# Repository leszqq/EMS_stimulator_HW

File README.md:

# EMS_stimulator_HW
Hardware for battery powered neuromuscular stimulator

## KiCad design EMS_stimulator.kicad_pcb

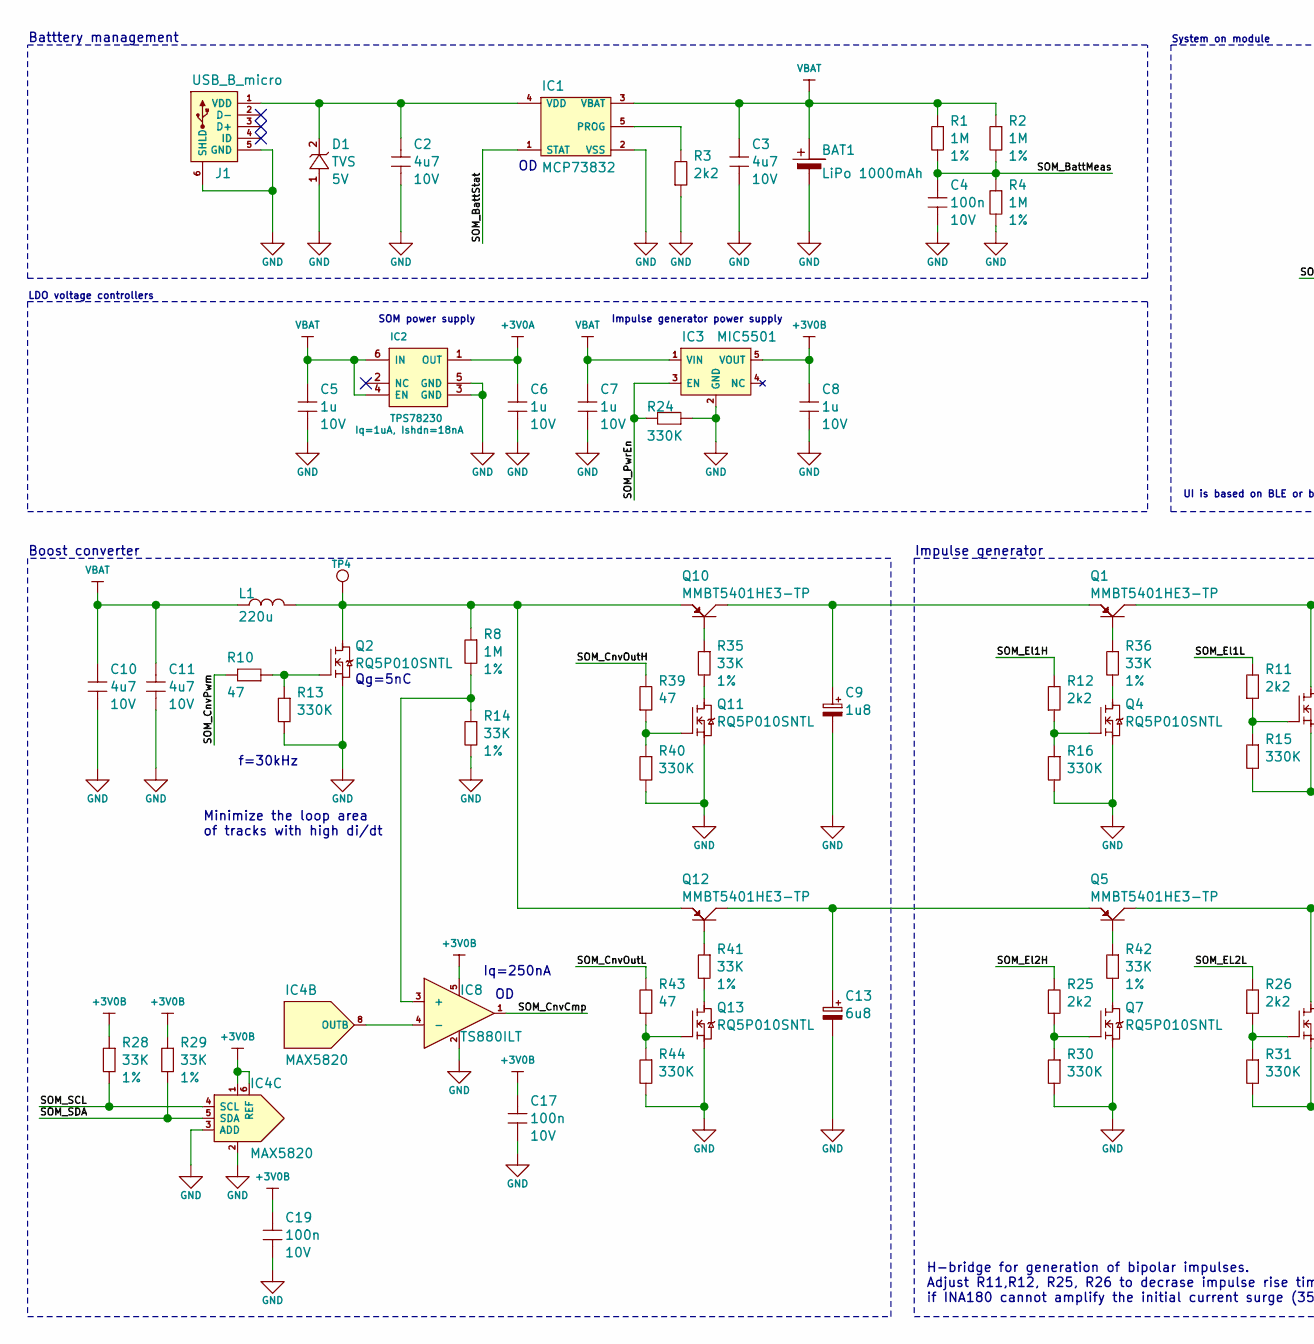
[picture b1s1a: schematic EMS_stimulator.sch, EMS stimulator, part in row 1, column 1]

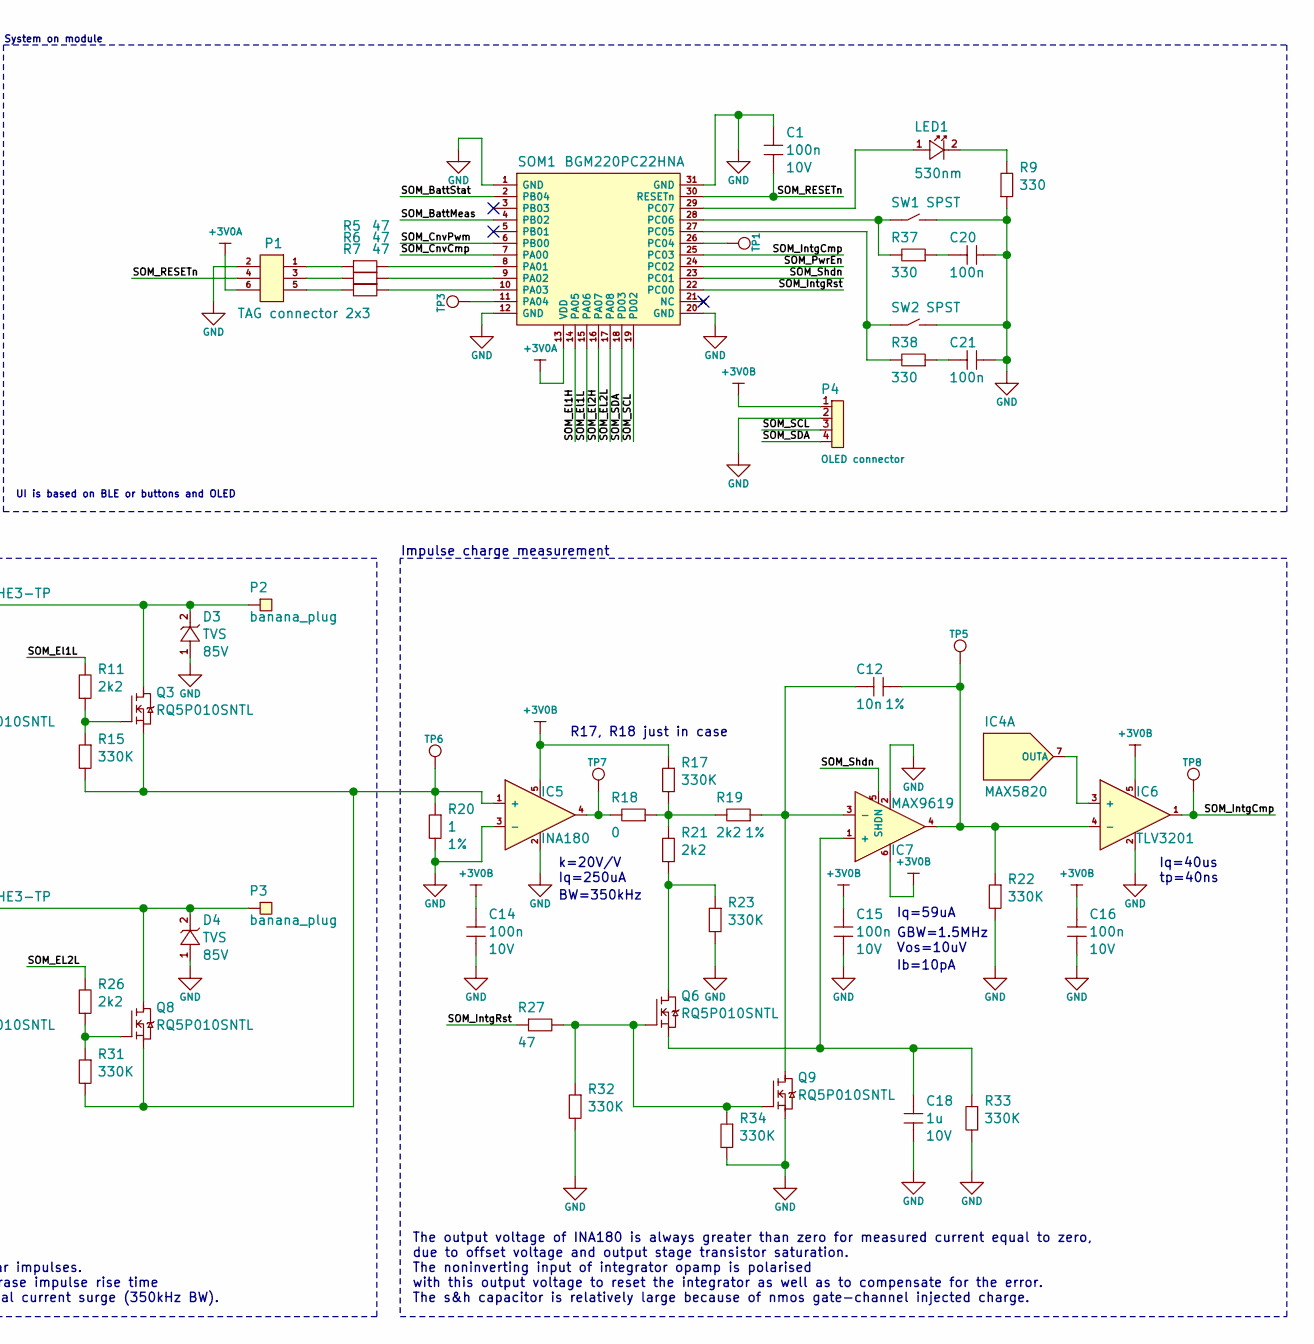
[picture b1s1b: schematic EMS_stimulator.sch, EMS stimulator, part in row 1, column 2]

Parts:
BAT1: LiPo 1000mAh; wire_solder_tht_pad-x2
C1, C4, C14, C15, C16, C17, C19, C20, C21: 100n; C0402
C2, C3, C10, C11: 4u7; C0402
C5, C6, C7, C8, C18: 1u; C0402
C9: 1u8; CAlu8.3mmx8.3mmx10mmSMD
C12: 10n; C0402
C13: 6u8; CAlu8.3mmx8.3mmx10mmSMD
D1: TVS; SMA
D3, D4: TVS; SOD-123FL
IC1: MCP73832; SOT-23-5
IC2: TPS78230; WSON-6-thermal
IC3: MIC5501; SOT-23-5
IC4: MAX5820; uMAX-8
IC5: INA180; SOT-23-5
IC6: TLV3201; SOT-23-5
IC7: MAX9619; SOT-363-6
IC8: TS880ILT; SOT-23-5
J1: USB_B_micro; AMPHENOL_10103594-0001LF
L1: 220u; L12.5mmx12.5mmx8mm
LED1: 530nm; D0402
P1: TAG connector 2x3; PinHeader_2x3
P2, P3: banana_plug; GC2010-M
P4: conn_p_1x4; PinHeader_1x4
Q1, Q5, Q10, Q12: PNP_BEC; SOT-23-3
Q2, Q3, Q4, Q6, Q7, Q8, Q9, Q11, Q13: NMOS; SOT-346
R1, R2, R4, R8: 1M; R0402
R3, R11, R12, R19, R21, R25, R26: 2k2; R0402
R5, R6, R7, R10, R27, R39, R43: 47; R0402
R9, R37, R38: 330; R0402
R13, R15, R16, R17, R22, R23, R24, R30, R31, R32, R33, R34, R40, R44: 330K; R0402
R14, R28, R29, R35, R36, R41, R42: 33K; R0402
R18: 0; R0402
R20: 1; R0402
SOM1: BGM220PC22HNA; BGM220P
SW1, SW2: SPST; KMS231GLFS
TP1, TP3, TP4, TP5, TP6, TP7, TP8: testPoint

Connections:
+3V0A: C6.1, IC2.1 (OUT), P1.6, SOM1.13 (VDD)
+3V0B: C8.1, C14.1, C15.1, C16.1, C17.1, C19.1, IC3.5 (VOUT), IC4.1, IC4.6 (REF), IC5.5, IC6.5, IC7.6, IC8.5, P4.1, R17.1, R28.1, R29.1
/SOM_BattMeas: C4.1, R1.2, R2.2, R4.1, SOM1.4 (PB02)
/SOM_BattStat: IC1.1 (STAT), SOM1.2 (PB04)
/SOM_CnvCmp: IC8.1, SOM1.7 (PA00)
/SOM_CnvOutH: R39.2
/SOM_CnvOutL: R43.2
/SOM_CnvPwm: R10.2, SOM1.6 (PB00)
/SOM_EL2L: R26.2, SOM1.17 (PA08)
/SOM_El1H: R12.2, SOM1.14 (PA05)
/SOM_El1L: R11.2, SOM1.15 (PA06)
/SOM_El2H: R25.2, SOM1.16 (PA07)
/SOM_IntgCmp: IC6.1, SOM1.25 (PC03), TP8.1
/SOM_IntgRst: R27.1, SOM1.22 (PC00)
/SOM_PwrEn: IC3.3 (EN), R24.2, SOM1.24 (PC02)
/SOM_RESETn: C1.2, P1.4, SOM1.30 (RESETn)
/SOM_SCL: IC4.4 (SCL), P4.3, R28.2, SOM1.19 (PD02)
/SOM_SDA: IC4.5 (SDA), P4.4, R29.2, SOM1.18 (PD03)
/SOM_Shdn: IC7.5 (SHDN), SOM1.23 (PC01)
GND: BAT1.2 (-), C1.1, C2.2, C3.2, C4.2, C5.2, C6.2, C7.2, C8.2, C9.2 (-), C10.2, C11.2, C13.2 (-), C14.2, C15.2, C16.2, C17.2, C18.2, C19.2, C20.1, C21.1, D1.1 (A), D3.1 (A), D4.1 (A), IC1.2 (VSS), IC2.3 (GND), IC2.5 (GND), IC3.2 (GND), IC4.2, IC4.3 (ADD), IC5.2, IC5.3 (-), IC6.2, IC7.2, IC8.2, J1.5 (GND), J1.6 (SHLD), P1.2, P4.2, Q2.2 (S), Q4.2 (S), Q7.2 (S), Q9.2 (S), Q11.2 (S), Q13.2 (S), R3.1, R4.2, R9.1, R13.2, R14.2, R16.2, R20.2, R22.2, R23.2, R24.1, R30.2, R32.2, R33.2, R34.2, R40.2, R44.2, SOM1.1 (GND), SOM1.12 (GND), SOM1.20 (GND), SOM1.31 (GND), SW1.2, SW2.2
unnamed: C2.1, D1.2 (C), IC1.4 (VDD), J1.1 (VDD)
unnamed: C9.1 (+), Q1.2 (E), Q10.3 (C)
unnamed: C12.1, IC6.4 (-), IC7.4, R22.1, TP5.1
unnamed: C12.2, IC7.3 (-), Q9.3 (D), R19.1
unnamed: C13.1 (+), Q5.2 (E), Q12.3 (C)
unnamed: C18.1, IC7.1 (+), Q6.2 (S), R33.1
unnamed: C20.2, R37.1
unnamed: C21.2, R38.1
unnamed: D3.2 (C), P2.1, Q1.3 (C), Q3.3 (D)
unnamed: D4.2 (C), P3.1, Q5.3 (C), Q8.3 (D)
unnamed: IC1.5 (PROG), R3.2
unnamed: IC4.7 (OUTA), IC6.3 (+)
unnamed: IC4.8 (OUTB), IC8.4 (-)
unnamed: IC5.1 (+), Q3.2 (S), Q8.2 (S), R15.2, R20.1, R31.2, TP6.1
unnamed: IC5.4, R18.2, TP7.1
unnamed: IC8.3 (+), R8.2, R14.1
unnamed: L1.2, Q2.3 (D), Q10.2 (E), Q12.2 (E), R8.1, TP4.1
unnamed: LED1.1 (A), SOM1.29 (PC07)
unnamed: LED1.2 (C), R9.2
unnamed: P1.1, R5.1
unnamed: P1.3, R6.1
unnamed: P1.5, R7.1
unnamed: Q1.1 (B), R36.1
unnamed: Q2.1 (G), R10.1, R13.1
unnamed: Q3.1 (G), R11.1, R15.1
unnamed: Q4.1 (G), R12.1, R16.1
unnamed: Q4.3 (D), R36.2
unnamed: Q5.1 (B), R42.1
unnamed: Q6.1 (G), Q9.1 (G), R27.2, R32.1, R34.1
unnamed: Q6.3 (D), R21.1, R23.1
unnamed: Q7.1 (G), R25.1, R30.1
unnamed: Q7.3 (D), R42.2
unnamed: Q8.1 (G), R26.1, R31.1
unnamed: Q10.1 (B), R35.1
unnamed: Q11.1 (G), R39.1, R40.1
unnamed: Q11.3 (D), R35.2
unnamed: Q12.1 (B), R41.1
unnamed: Q13.1 (G), R43.1, R44.1
unnamed: Q13.3 (D), R41.2
unnamed: R5.2, SOM1.8 (PA01)
unnamed: R6.2, SOM1.9 (PA02)
unnamed: R7.2, SOM1.10 (PA03)
unnamed: R17.2, R18.1, R19.2, R21.2
unnamed: R37.2, SOM1.28 (PC06), SW1.1
unnamed: R38.2, SOM1.27 (PC05), SW2.1
unnamed: SOM1.11 (PA04), TP3.1
unnamed: SOM1.26 (PC04), TP1.1
VBAT: BAT1.1 (+), C3.1, C5.1, C7.1, C10.1, C11.1, IC1.3 (VBAT), IC2.4 (EN), IC2.6 (IN), IC3.1 (VIN), L1.1, R1.1, R2.1

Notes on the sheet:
Batttery management
LDO voltage controllers
SOM power supply
Impulse generator power supply
f=30kHz
Boost converter
Impulse generator
Impulse charge measurement
H-bridge for generation of bipolar impulses. Adjust R11,R12, R25, R26 to decrase impulse rise time if INA180 cannot amplify the initial current surge (350kHz BW).
Iq=250nA
Qg=5nC
k=20V/V Iq=250uA
Iq=59uA
Iq=40us tp=40ns
The output voltage of INA180 is always greater than zero for measured current equal to zero, due to offset voltage and output stage transistor saturation. The noninverting input of integrator opamp is polarised with this output voltage to reset the integrator as well as to compensate for the error.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
System on module
UI is based on BLE or buttons and OLED
BW=350kHz
GBW=1.5MHz Vos=10uV
Ib=10pA
R17, R18 just in case
Minimize the loop area of tracks with high di/dt

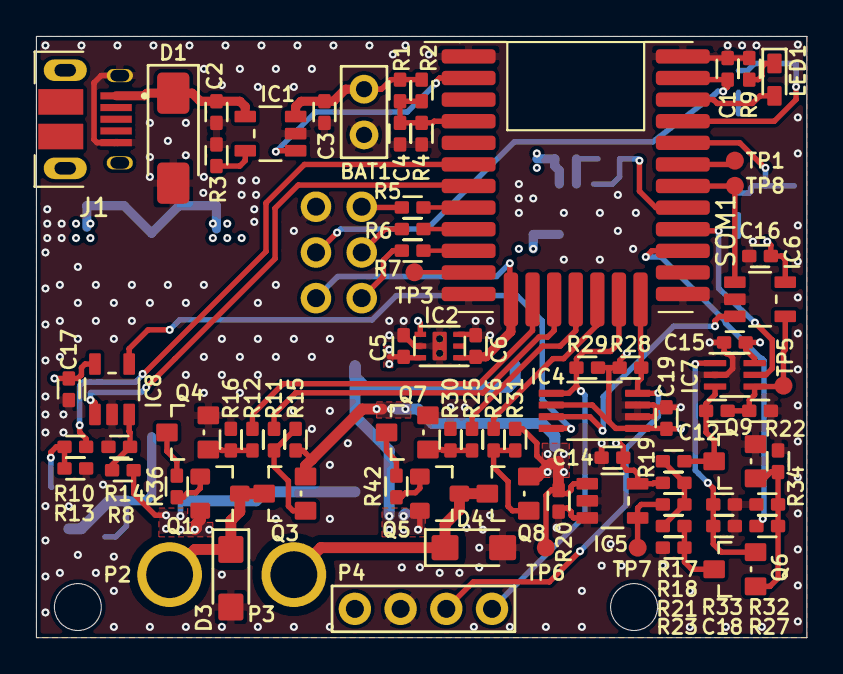
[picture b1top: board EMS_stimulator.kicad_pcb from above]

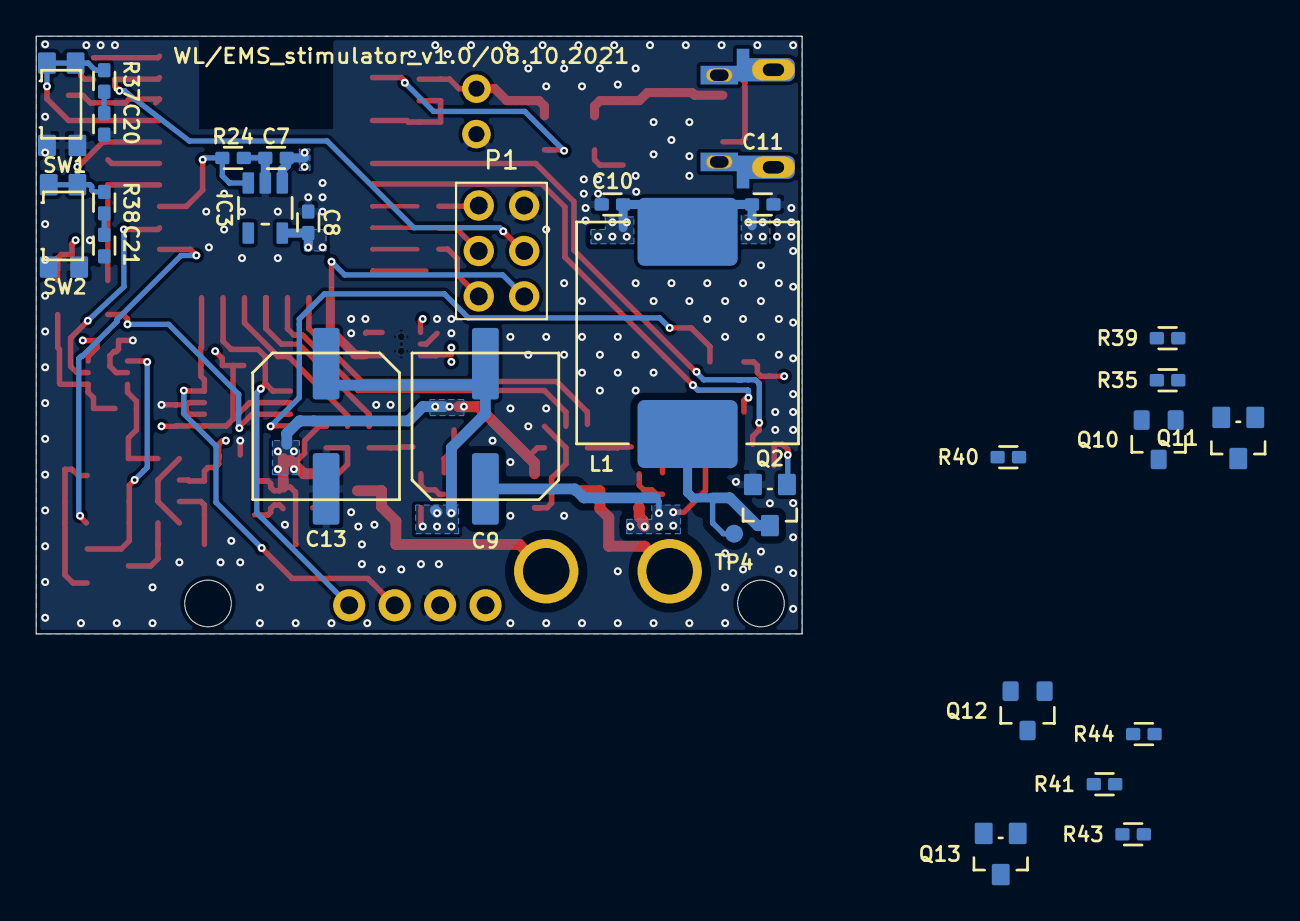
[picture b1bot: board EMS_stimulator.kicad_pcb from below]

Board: 4 copper layers, 42.8 x 33.4 mm, 107 parts (28 on the bottom side), 66 nets.

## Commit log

2021-10-14 Add v1.0 schematic, PCB layout, and production files.
2021-10-16 Update schematic with switches neccesary to generate two different voltages on separate capacitors.
